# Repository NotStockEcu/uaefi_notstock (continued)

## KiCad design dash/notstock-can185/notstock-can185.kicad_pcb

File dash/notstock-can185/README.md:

# NOT STOCK CAN 1.85

A round board that sits behind the **Waveshare ESP32-S3-Touch-LCD-1.85**
(SKU 28514) on its three M2 holes and turns the car's OBD supply and CAN
into what the round gauge needs. One 4-wire cable from the OBD plug; to
the display the 4-wire cable that comes with it (CAN) and two wires
(power), all soldered to pads on this board.

KiCad 7 project: `notstock-can185.kicad_pro` (schematic, PCB). The KiCad
schematic joins pins by net labels (same name, same net): PDF in
[docs/schematic.pdf](docs/schematic.pdf). The same circuit drawn with wires,
for reading: [docs/readable.png](docs/readable.png). Placement:
[docs/assembly.png](docs/assembly.png).

**State: rev 7, designed, DRC clean (0 errors, 0 unconnected), ready to
order with assembly. Rev 6 built and in the car: the display's touch
needed a hard press there (fine on USB at home), and the PH connector was
hard to crimp. Rev 7: a second LC stage on the display's supply (L2, C9,
C10, C11) and a JST XH 2.5 mm for J1. Rev 4 built (JLCPCB, assembled): the regulator holds
3.8 V on J3 from about 4 V to 14.4 V in (bench, no load); with the display,
the CAN side and in the car not tried yet.** Rev 4 feeds the display through its
battery socket instead of its USB-C (no room for a USB cable). Rev 6
takes its 12 V from OBD pin 1 (terminal 15): on and off with the key.

## How it connects

The display has no plug-on header. What it has, and what this board uses
(Waveshare's schematic and drawing of the board, `ESP32-S3-LCD-1.85`):

| Display | Cable | This board |
| --- | --- | --- |
| battery socket J1, MX1.25 2-pin (1 BAT, 2 GND); seen from the back with the USB-C down, the 2-pin socket on the left | MX1.25 2-pin plug with wires, or two wires soldered to the socket's pins | J3 pads: "+" to BAT, "-" to GND, 3.75 V |
| UART socket, 4-pin 1.0 mm, bottom right (1 RXD/GPIO44, 2 TXD/GPIO43, 3 3V3, 4 GND) | the 4-wire cable that comes with the display, free ends cut to length | J2 pads, marked with the display's names: IO44, IO43, 3V3, GND (CAN, and the display's 3.3 V for the transceiver) |
| three M2 holes (15.73 left, 14.10 up / 14.90 down; 21.27 right) | M2 spacers, 6 to 8 mm | H1..H3 |

The car: J1, JST XH 4-pin, vertical, through hole (12V, GND, CAN-H, CAN-L, marked on the
board).

## On and off with the key: OBD pin 1

OBD pin 16 is permanent +12 V. Pin 1 is free for the maker; VW puts
terminal 15 there (+12 V switched by the key; measured on this T5.1, and
the CANcheck display is powered from it too). The board takes its 12 V
from pin 1, not 16: on with the key, off without it, nothing drawn when
parked. About 0.1 A at 12 V. Terminal 15 stays on while cranking; the
regulator runs down to 4 V input, so the display rides through the dip.

## What is on it

| Block | Parts |
| --- | --- |
| Input | J1 JST XH 4-pin (2.5 mm) through hole, vertical; F1 0.5 A resettable fuse; D1 SS34 against reverse polarity; D2 SMAJ26A against load dump |
| 12 V -> 3.75 V | U1 LMR16006YDDCR (60 V, 0.6 A, 2.1 MHz), L1 22 uH, D3 K16 (60 V 1 A Schottky), 2 x 22 uF out; 39 k / 10 k sets 3.75 V |
| Filter | L2 1 uH, C9 C10 22 uF, C11 100 nF: the regulator's 2.1 MHz some 70 dB down before the display (corner about 30 kHz; the feedback stays before it) |
| 3.75 V out | J3, two solder pads for the wires to the display's battery socket |
| CAN | U2 SN65HVD230 (3.3 V from the display's UART socket, Rs to GND: full speed); D4 NUP2105L ESD; R4/R5/C8 split termination behind JP1, open, not assembled; R6 1 k in RXD |
| Mechanics | Ø 48 mm like the display, the display's three M2 holes |

Termination: JP1 open, R4/R5/C8 not assembled. Measure the resistance
between OBD pins 6 and 14 with the key out: about 60 R, the bus is
terminated at both ends and nothing is needed; about 120 R, only one end
is (on the power box, the T5.1 needed a 120 R at the OBD end to talk):
solder R4 and R5 (any 0805 56..62 R) and bridge JP1, C8 optional.

## Cable to the car

JST XHP-4 housing with SXH-001T-P0.6 crimps on the board side (XH
crimps are bigger than PH and easier by hand; ready-made "XH 2.54 4P"
leads with the crimps on save the crimping); at the OBD
plug: pin 1 +12 V (terminal 15, not pin 16), pin 4 or 5 GND, pin 6
CAN-H, pin 14 CAN-L. CAN-H and
CAN-L twisted.

## Check before ordering

- Which wire is which on the display's cable: the colours mean nothing.
  Plugged into the display, powered from its USB: 3.3 V between the 3V3
  wire and the GND wire. With the display unpowered, the GND wire beeps to
  the USB-C shell. Of the other two, IO44 is on socket pin 1 (next to the
  edge marked 1 or the triangle on the display's silkscreen).
- The battery plug's polarity: ready-made MX1.25 cables come both ways.
  Red is not proof: with the plug in the display, the wire on the
  display's "+" (or BAT) side goes to J3 "+".
- Height: the spacers must clear the display's tallest parts (USB-C, SD
  slot, the 1.0 mm sockets, about 4.5 mm) plus the cables' plugs. The wire
  pads are through holes: solder the wires from the display's side, or
  from the back with the ends trimmed flat.
- Waveshare's drawing was the source of the outline and the holes; hold
  the printed board (1:1 PDF of `docs/top.svg`) against the display first.

## Make it (JLCPCB, with assembly)

Three files in `fab/`:

| File | Where on JLCPCB |
| --- | --- |
| `notstock-can185-gerbers.zip` | "Add gerber file": 2 layers, 1.6 mm, any colour |
| `bom.csv` | PCB Assembly, "Add BOM File" |
| `cpl.csv` | PCB Assembly, "Add CPL File" |

Assembly: top side only, all SMD but J1, a through-hole part: JLCPCB
fits it too (THT assembly, a small extra), or leave it out of the order
and solder its 4 pins by hand. Its pins come out on the display's side:
cut them short (about 1 mm). Every part has its LCSC number in
`bom.csv` (also in the schematic and on the footprints, field "LCSC"):

| Ref | Part | LCSC |
| --- | --- | --- |
| U1 | TI LMR16006YDDCR | C290195 |
| U2 | TI SN65HVD230DR | C12084 |
| D4 | onsemi NUP2105LT1G | C14486 |
| D1 | SS34 (MDD) | C8678 |
| D2 | SMAJ26A | C383018 |
| D3 | GOODWORK K16 (60 V 1 A, SOD-123FL) | C2943756 |
| F1 | SMD1812P050TF/30 (RUILON) | C12559 |
| L1 | Sunlord SWPA4026S220MT | C88254 |
| L2 | Sunlord SWPA4026S1R0NT (1 uH) | C96890 |
| J1 | JST B4B-XH-A(LF)(SN) (vertical, through hole) | C144395 |
| C1 | 4.7 uF 50 V 1206 (Murata) | C77096 |
| C2, C3, C6, C7, C11 | 100 nF 50 V 0603 (YAGEO) | C14663 |
| C4, C5, C9, C10 | 22 uF 16 V 1206 (Samsung) | C90146 |
| R1 | 100 k 0603 | C25803 |
| R2 | 39 k 0603 | C23153 |
| R3 | 10 k 0603 | C25804 |
| R6 | 1 k 0603 | C21190 |

R4, R5 and C8 (the split termination) are not assembled: with JP1 open
they do nothing, and the car's bus is terminated already. For a bench
without a terminator solder them by hand: R4, R5 any 0805 56..62 R 1 %, C8
4.7 nF 0603 (C53987), then bridge JP1.

JP1 is a solder bridge, J2 and J3 pads for wires: not parts. Stock changes: JLCPCB marks a part out
of stock in the BOM step; pick an equivalent there (same value, package,
voltage). The passives and D1 (SS34, C8678) are JLCPCB basic parts, the rest
extended (a small loading fee each). C4, C5, C9, C10 stay 1206 here (the built rev 4
layout); on the 1.32 board they are the basic 0805 C45783.

In the placement preview, check the parts with a direction: U1 (pin 1 dot),
U2 (pin 1 at the notch), D4, J1 (pin 1 square, 12V), D1/D2/D3 (the band towards the "K" side of the
footprint's silkscreen). KiCad and JLCPCB do not always agree on rotations; turn any
that are off in 90° steps there.

## Regenerate

Everything is generated from `tools/design.py` (parts, nets, positions):

```
python3 tools/gen_sch.py                       # the schematic
kicad-cli sch export netlist -o /tmp/n.net notstock-can185.kicad_sch
python3 tools/check_net.py /tmp/n.net          # schematic = design.py
python3 tools/gen_pcb.py --freerouting freerouting-2.0.1.jar
python3 tools/drc_summary.py                   # DRC of the routed board
python3 tools/gen_fab.py                       # fab/ and docs/
python3 tools/gen_readable.py                  # docs/readable.svg
```

Needs KiCad 7 with its python module and libraries, Java 21 and
[Freerouting](https://github.com/freerouting/freerouting) 2.x for the
routing. Freerouting is not deterministic: each run gives a different (and
DRC-checked) routing. Opened in KiCad, the project behaves like any other;
the generators overwrite manual changes, so after editing by hand stop
using them.

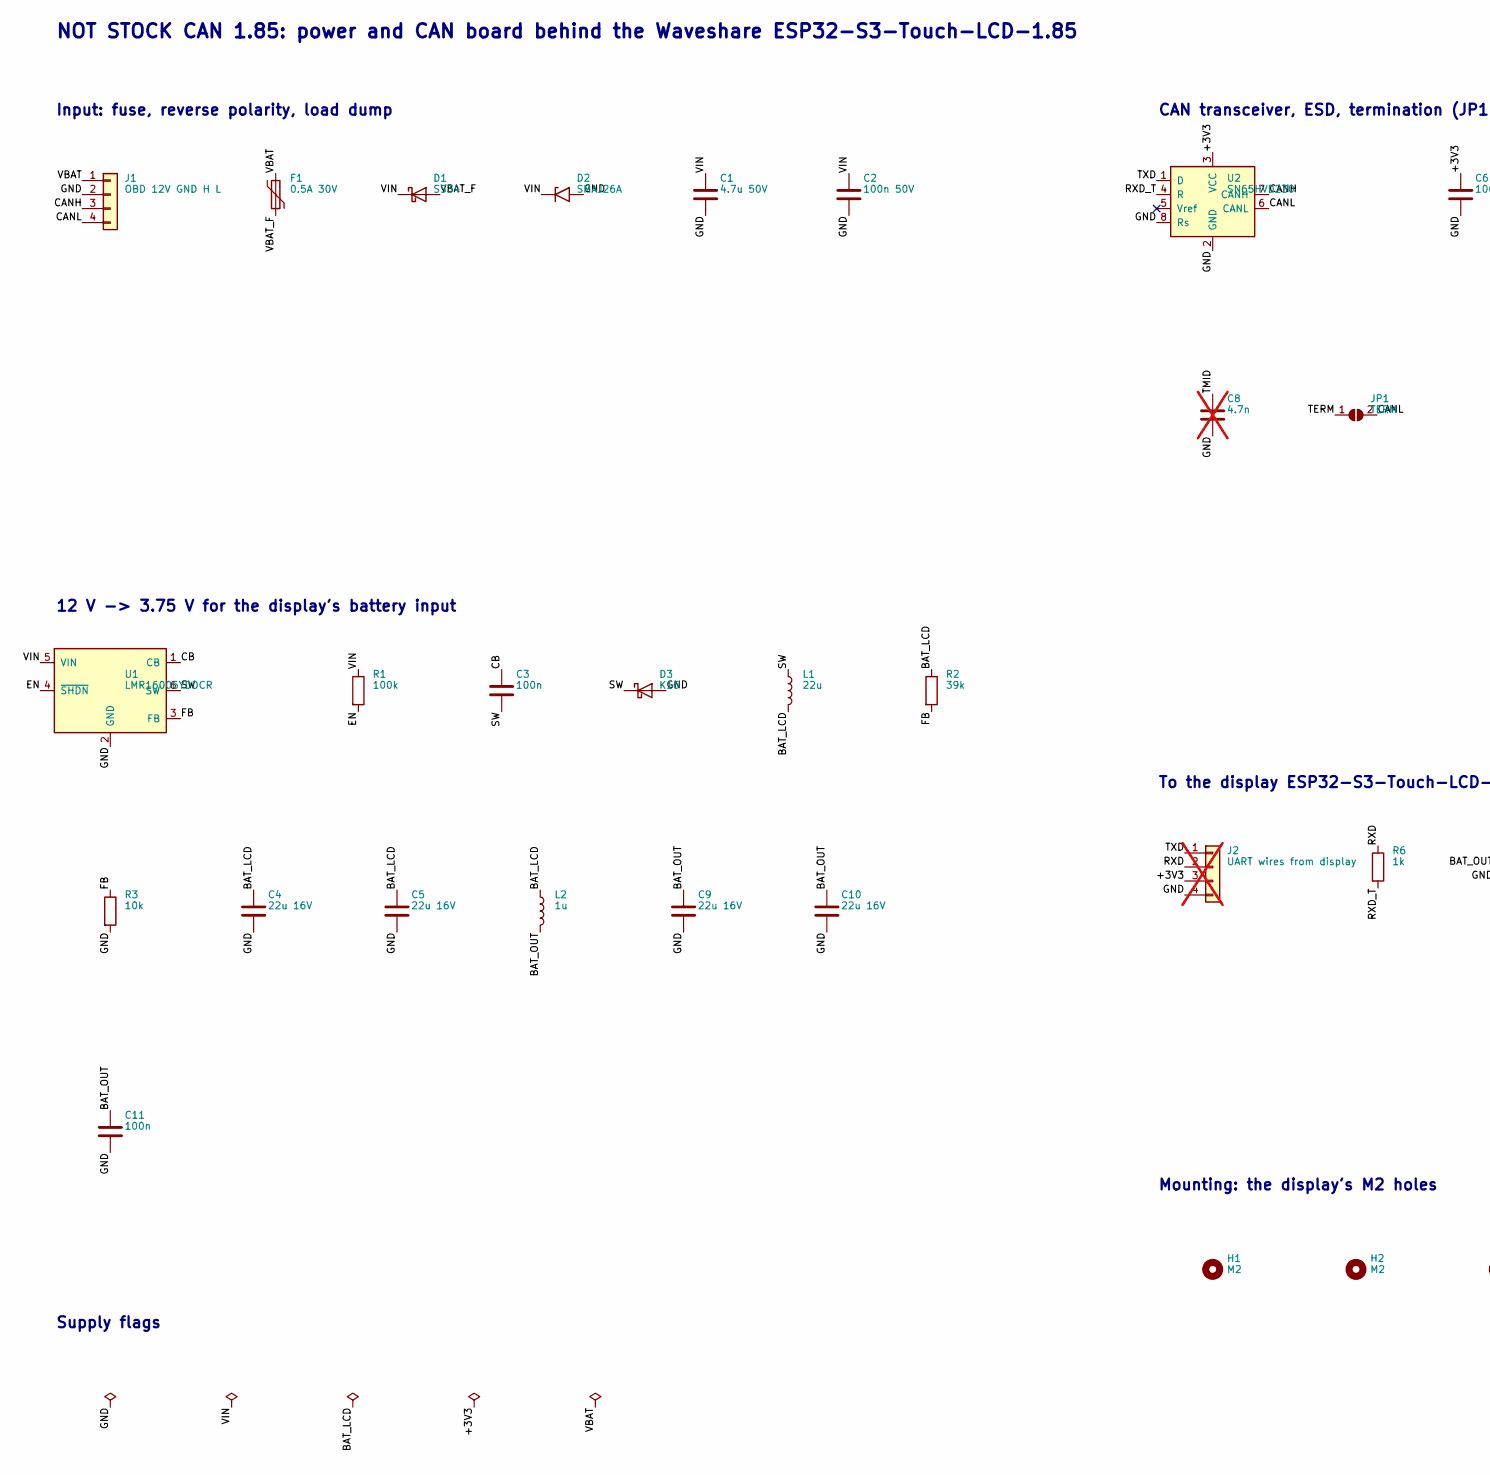
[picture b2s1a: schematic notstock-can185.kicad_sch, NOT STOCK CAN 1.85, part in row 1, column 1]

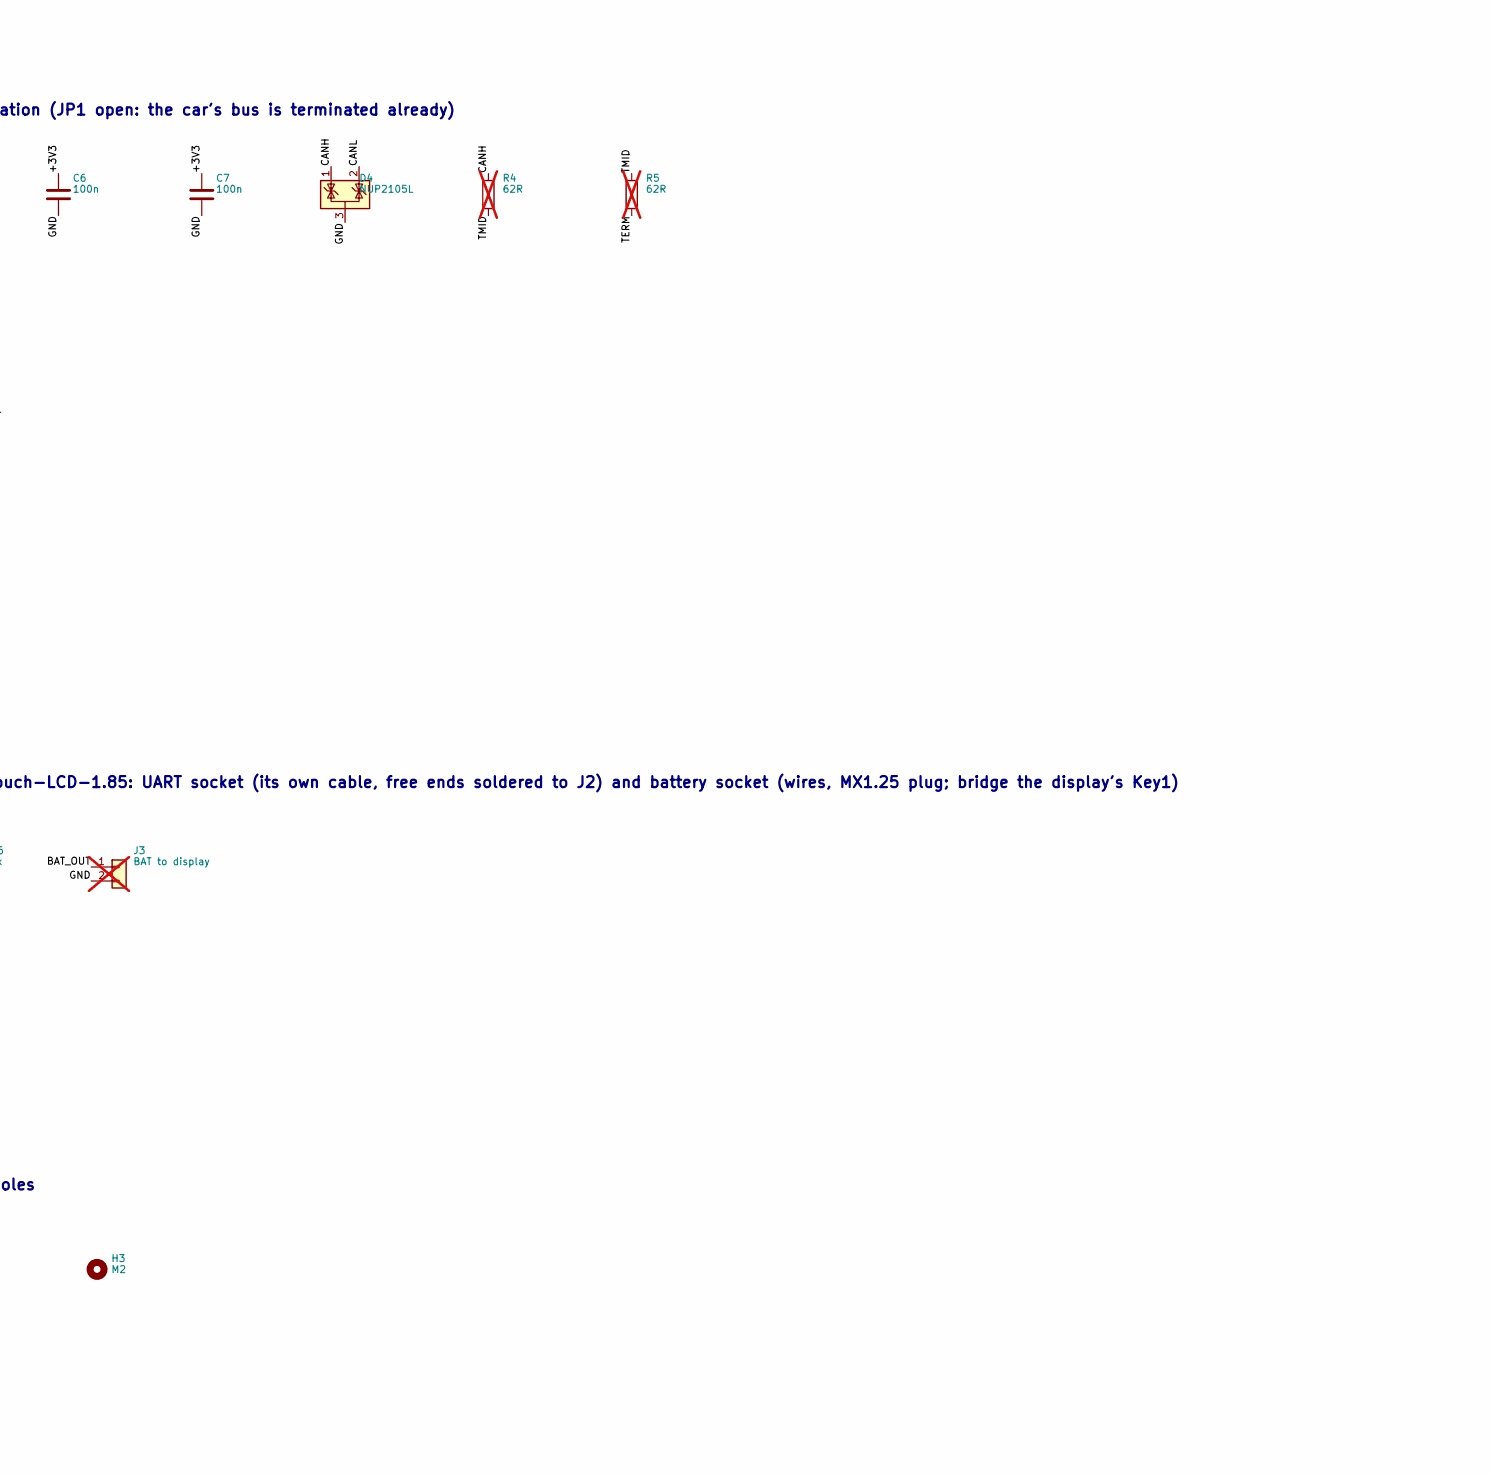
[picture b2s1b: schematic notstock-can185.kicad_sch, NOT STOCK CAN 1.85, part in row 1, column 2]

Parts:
C1: 4.7u 50V; C_1206_3216Metric; MPN Murata GRM31CR71H475KA12L (4.7 uF 50 V 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; LCSC C77096
C2: 100n 50V; C_0603_1608Metric; MPN YAGEO CC0603KRX7R9BB104 (100 nF 50 V); LCSC C14663
C3, C6, C7, C11: 100n; C_0603_1608Metric; MPN YAGEO CC0603KRX7R9BB104 (100 nF 50 V); LCSC C14663
C4, C5, C9, C10: 22u 16V; C_1206_3216Metric; MPN Samsung CL31A226KOHNNNE (22 uF 16 V X5R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; LCSC C90146
C8: 4.7n; C_0603_1608Metric; MPN FH 0603B472K500NT (4.7 nF 50 V X7R); LCSC C53987; not fitted
D1: SS34; D_SMA; MPN MDD SS34 (40 V 3 A); LCSC C8678
D2: SMAJ26A; D_SMA; MPN SMAJ26A; LCSC C383018
D3: K16; D_SOD-123F; MPN GOODWORK K16 (60 V 1 A Schottky, SOD-12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; LCSC C2943756
D4: NUP2105L; SOT-23; MPN onsemi NUP2105LT1G; LCSC C14486
F1: 0.5A 30V; Fuse_1812_4532Metric; MPN RUILON SMD1812P050TF/30 (0.5 A, 30 V); LCSC C12559
H1, H2, H3: M2; MountingHole_2.2mm_M2; MPN M2
J1: OBD 12V GND H L; JST_XH_B4B-XH-A_1x04_P2.50mm_Vertical; MPN JST B4B-XH-A(LF)(SN); LCSC C144395
J2: UART wires from display; SolderWire-0.15sqmm_1x04_P4mm_D0.5mm_OD1.5mm; MPN (wires); not fitted
J3: BAT to display; SolderWire-0.25sqmm_1x02_P4.2mm_D0.65mm_OD1.7mm; MPN (wires); not fitted
JP1: TERM; SolderJumper-2_P1.3mm_Open_Pad1.0x1.5mm; MPN (solder bridge)
L1: 22u; L_Sunlord_SWPA4026S; MPN Sunlord SWPA4026S220MT (22 uH); LCSC C88254
L2: 1u; L_Sunlord_SWPA4026S; MPN Sunlord SWPA4026S1R0NT (1 uH 3 A); LCSC C96890
R1: 100k; R_0603_1608Metric; MPN UNI-ROYAL 0603WAF1003T5E (100 k 1%); LCSC C25803
R2: 39k; R_0603_1608Metric; MPN UNI-ROYAL 0603WAF3902T5E (39 k 1%); LCSC C23153
R3: 10k; R_0603_1608Metric; MPN UNI-ROYAL 0603WAF1002T5E (10 k 1%); LCSC C25804
R4, R5: 62R; R_0805_2012Metric; MPN 62 R 1% 0805; not fitted
R6: 1k; R_0603_1608Metric; MPN UNI-ROYAL 0603WAF1001T5E (1 k 1%); LCSC C21190
U1: LMR16006YDDCR; SOT-23-6; MPN TI LMR16006YDDCR; LCSC C290195
U2: SN65HVD230; SOIC-8_3.9x4.9mm_P1.27mm; MPN TI SN65HVD230DR; LCSC C12084

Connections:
+3V3: C6.1, C7.1, J2.3, U2.3 (VCC)
BAT_LCD: C4.1, C5.1, L1.2, L2.1, R2.1
BAT_OUT: C9.1, C10.1, C11.1, J3.1, L2.2
CANH: D4.1 (K), J1.3, R4.1, U2.7 (CANH)
CANL: D4.2 (K), J1.4, JP1.2 (B), U2.6 (CANL)
CB: C3.1, U1.1 (CB)
EN: R1.2, U1.4 (~SHDN)
FB: R2.2, R3.1, U1.3 (FB)
GND: C1.2, C2.2, C4.2, C5.2, C6.2, C7.2, C8.2, C9.2, C10.2, C11.2, D2.2 (A2), D3.2 (A), D4.3 (A), J1.2, J2.4, J3.2, R3.2, U1.2 (GND), U2.2 (GND), U2.8 (Rs)
RXD: J2.2, R6.1
RXD_T: R6.2, U2.4 (R)
SW: C3.2, D3.1 (K), L1.1, U1.6 (SW)
TERM: JP1.1 (A), R5.2
TMID: C8.1, R4.2, R5.1
TXD: J2.1, U2.1 (D)
VBAT: F1.1, J1.1
VBAT_F: D1.2 (A), F1.2
VIN: C1.1, C2.1, D1.1 (K), D2.1 (A1), R1.1, U1.5 (VIN)

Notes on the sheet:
Input: fuse, reverse polarity, load dump
12 V -> 3.75 V for the display's battery input
CAN transceiver, ESD, termination (JP1 open: the car's bus is terminated already)
To the display ESP32-S3-Touch-LCD-1.85: UART socket (its own cable, free ends soldered to J2) and battery socket (wires, MX1.25 plug; bridge the display's Key1)
Mounting: the display's M2 holes
NOT STOCK CAN 1.85: power and CAN board behind the Waveshare ESP32-S3-Touch-LCD-1.85
Supply flags

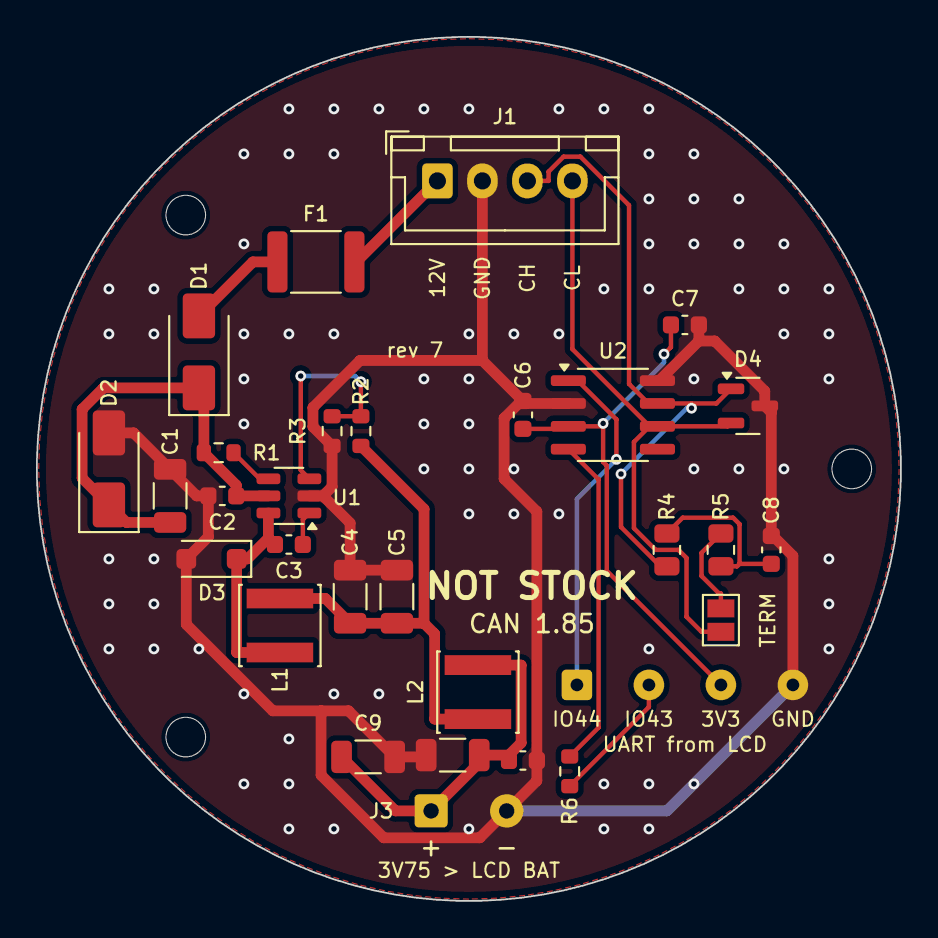
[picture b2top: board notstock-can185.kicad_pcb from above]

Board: 2 copper layers, 48.0 x 48.0 mm, 33 parts (0 on the bottom side), 18 nets.

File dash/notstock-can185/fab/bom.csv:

Comment,Designator,Footprint,LCSC Part #
Murata GRM31CR71H475KA12L (4.7 uF 50 V X7R 1206),C1,C_1206_3216Metric,C77096
YAGEO CC0603KRX7R9BB104 (100 nF 50 V),"C11,C2,C3,C6,C7",C_0603_1608Metric,C14663
Samsung CL31A226KOHNNNE (22 uF 16 V X5R 1206),"C10,C4,C5,C9",C_1206_3216Metric,C90146
MDD SS34 (40 V 3 A),D1,D_SMA,C8678
SMAJ26A,D2,D_SMA,C383018
"GOODWORK K16 (60 V 1 A Schottky, SOD-123FL)",D3,D_SOD-123F,C2943756
onsemi NUP2105LT1G,D4,SOT-23,C14486
"RUILON SMD1812P050TF/30 (0.5 A, 30 V)",F1,Fuse_1812_4532Metric,C12559
JST B4B-XH-A(LF)(SN),J1,JST_XH_B4B-XH-A_1x04_P2.50mm_Vertical,C144395
Sunlord SWPA4026S220MT (22 uH),L1,L_Sunlord_SWPA4026S,C88254
Sunlord SWPA4026S1R0NT (1 uH 3 A),L2,L_Sunlord_SWPA4026S,C96890
UNI-ROYAL 0603WAF1003T5E (100 k 1%),R1,R_0603_1608Metric,C25803
UNI-ROYAL 0603WAF3902T5E (39 k 1%),R2,R_0603_1608Metric,C23153
UNI-ROYAL 0603WAF1002T5E (10 k 1%),R3,R_0603_1608Metric,C25804
UNI-ROYAL 0603WAF1001T5E (1 k 1%),R6,R_0603_1608Metric,C21190
TI LMR16006YDDCR,U1,SOT-23-6,C290195
TI SN65HVD230DR,U2,SOIC-8_3.9x4.9mm_P1.27mm,C12084

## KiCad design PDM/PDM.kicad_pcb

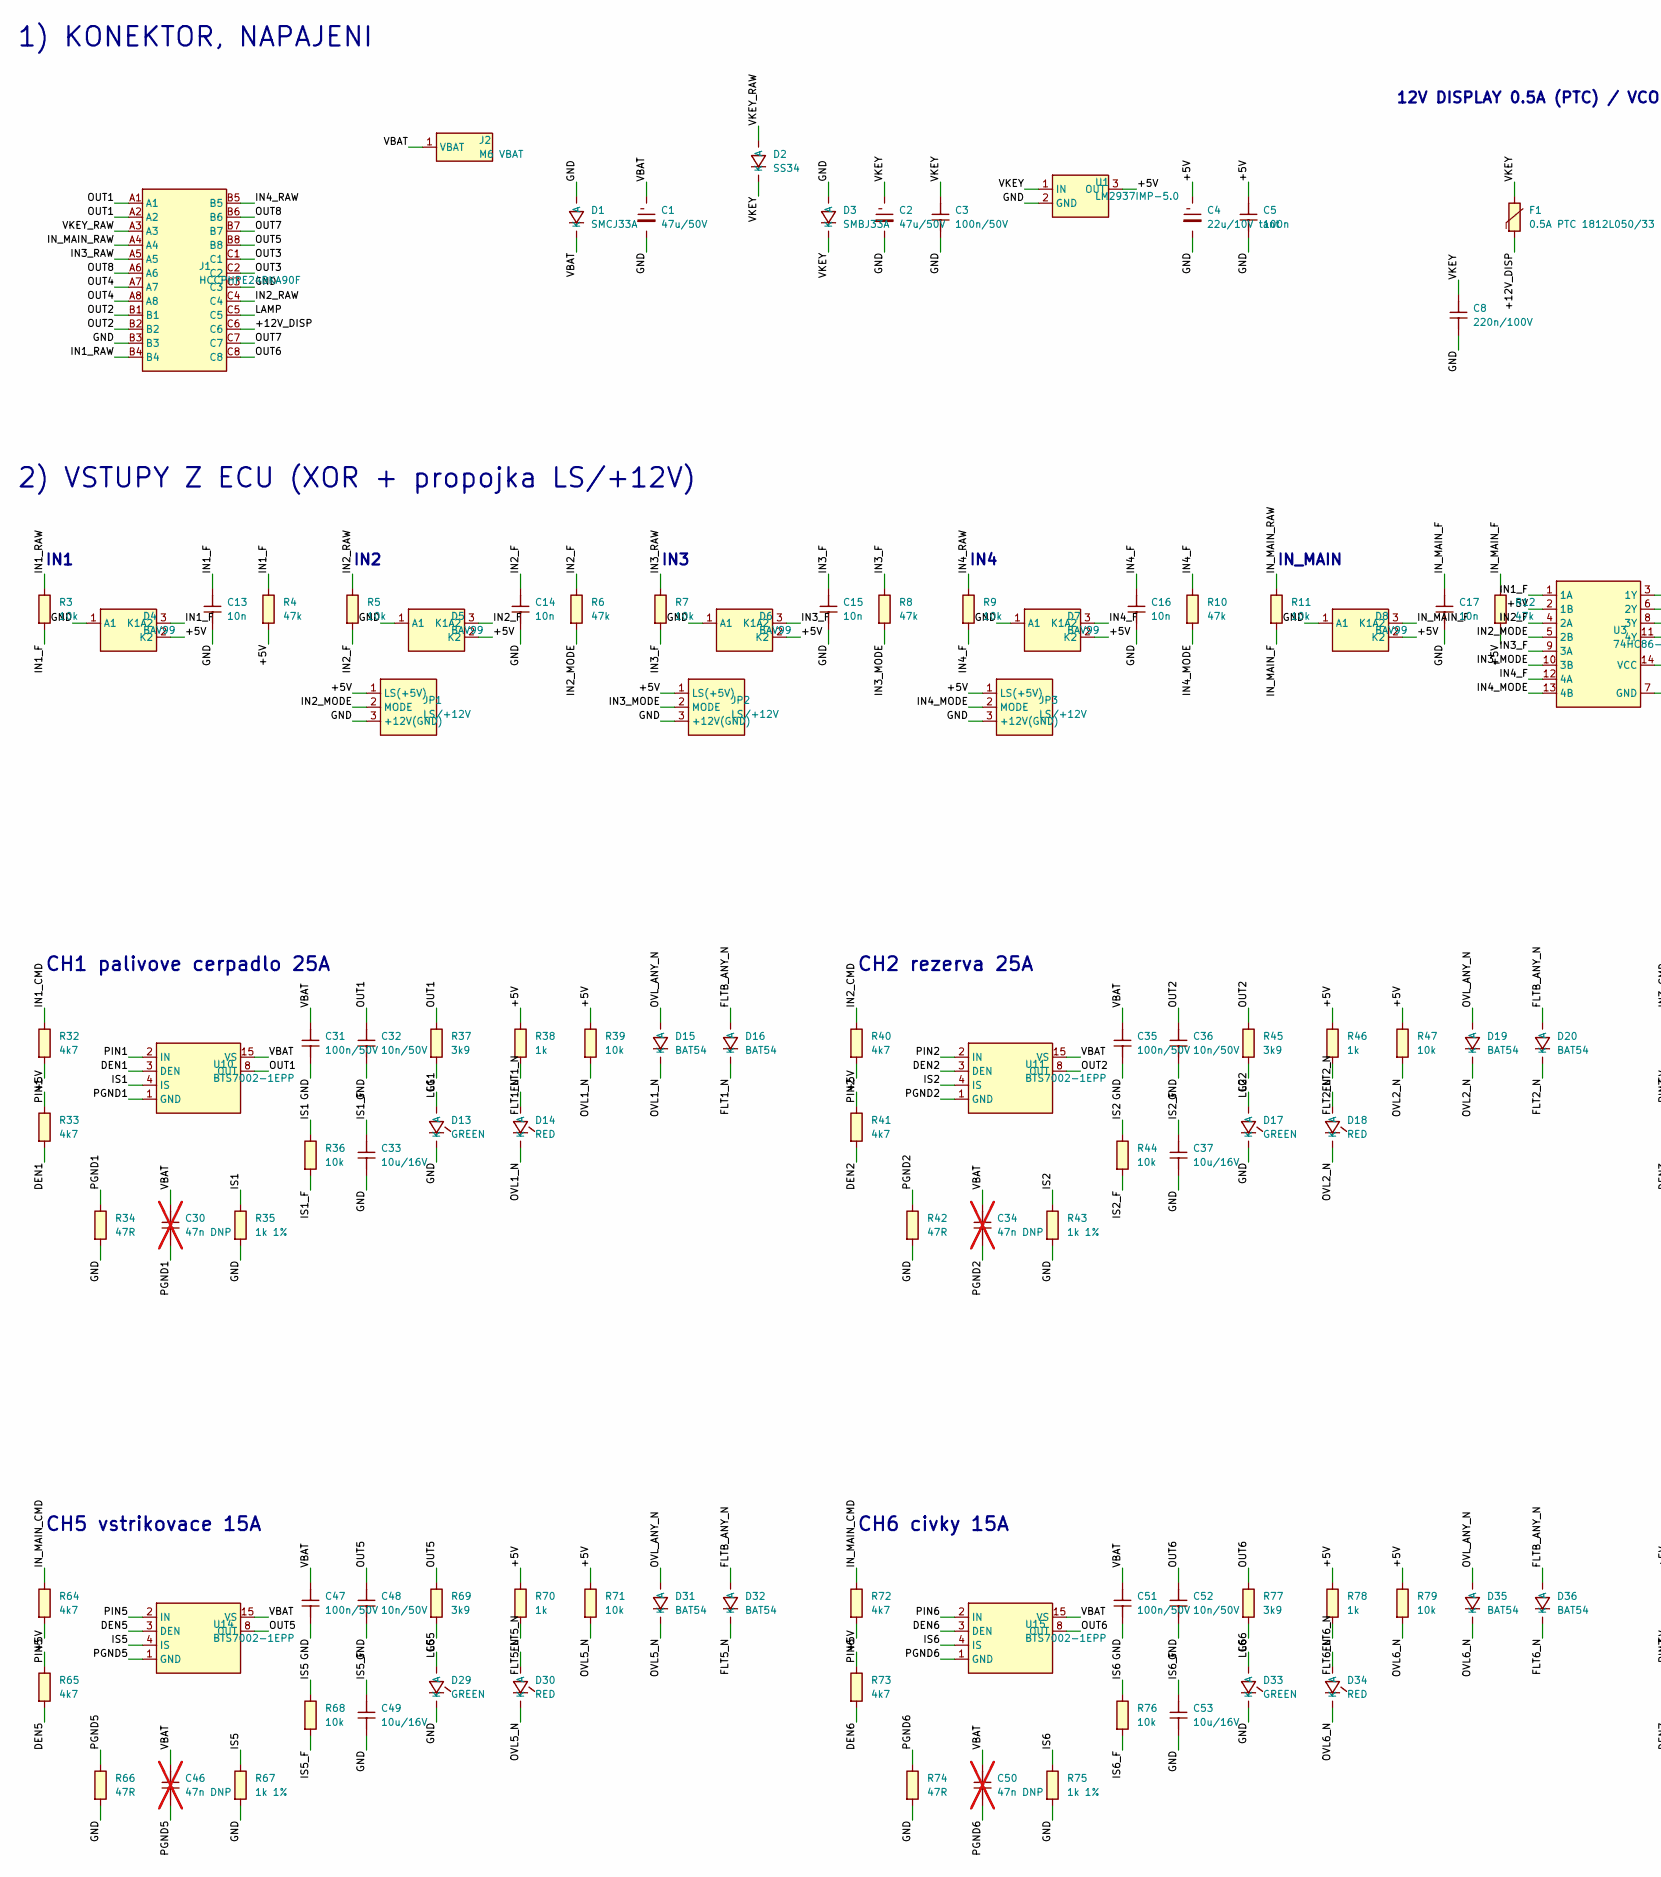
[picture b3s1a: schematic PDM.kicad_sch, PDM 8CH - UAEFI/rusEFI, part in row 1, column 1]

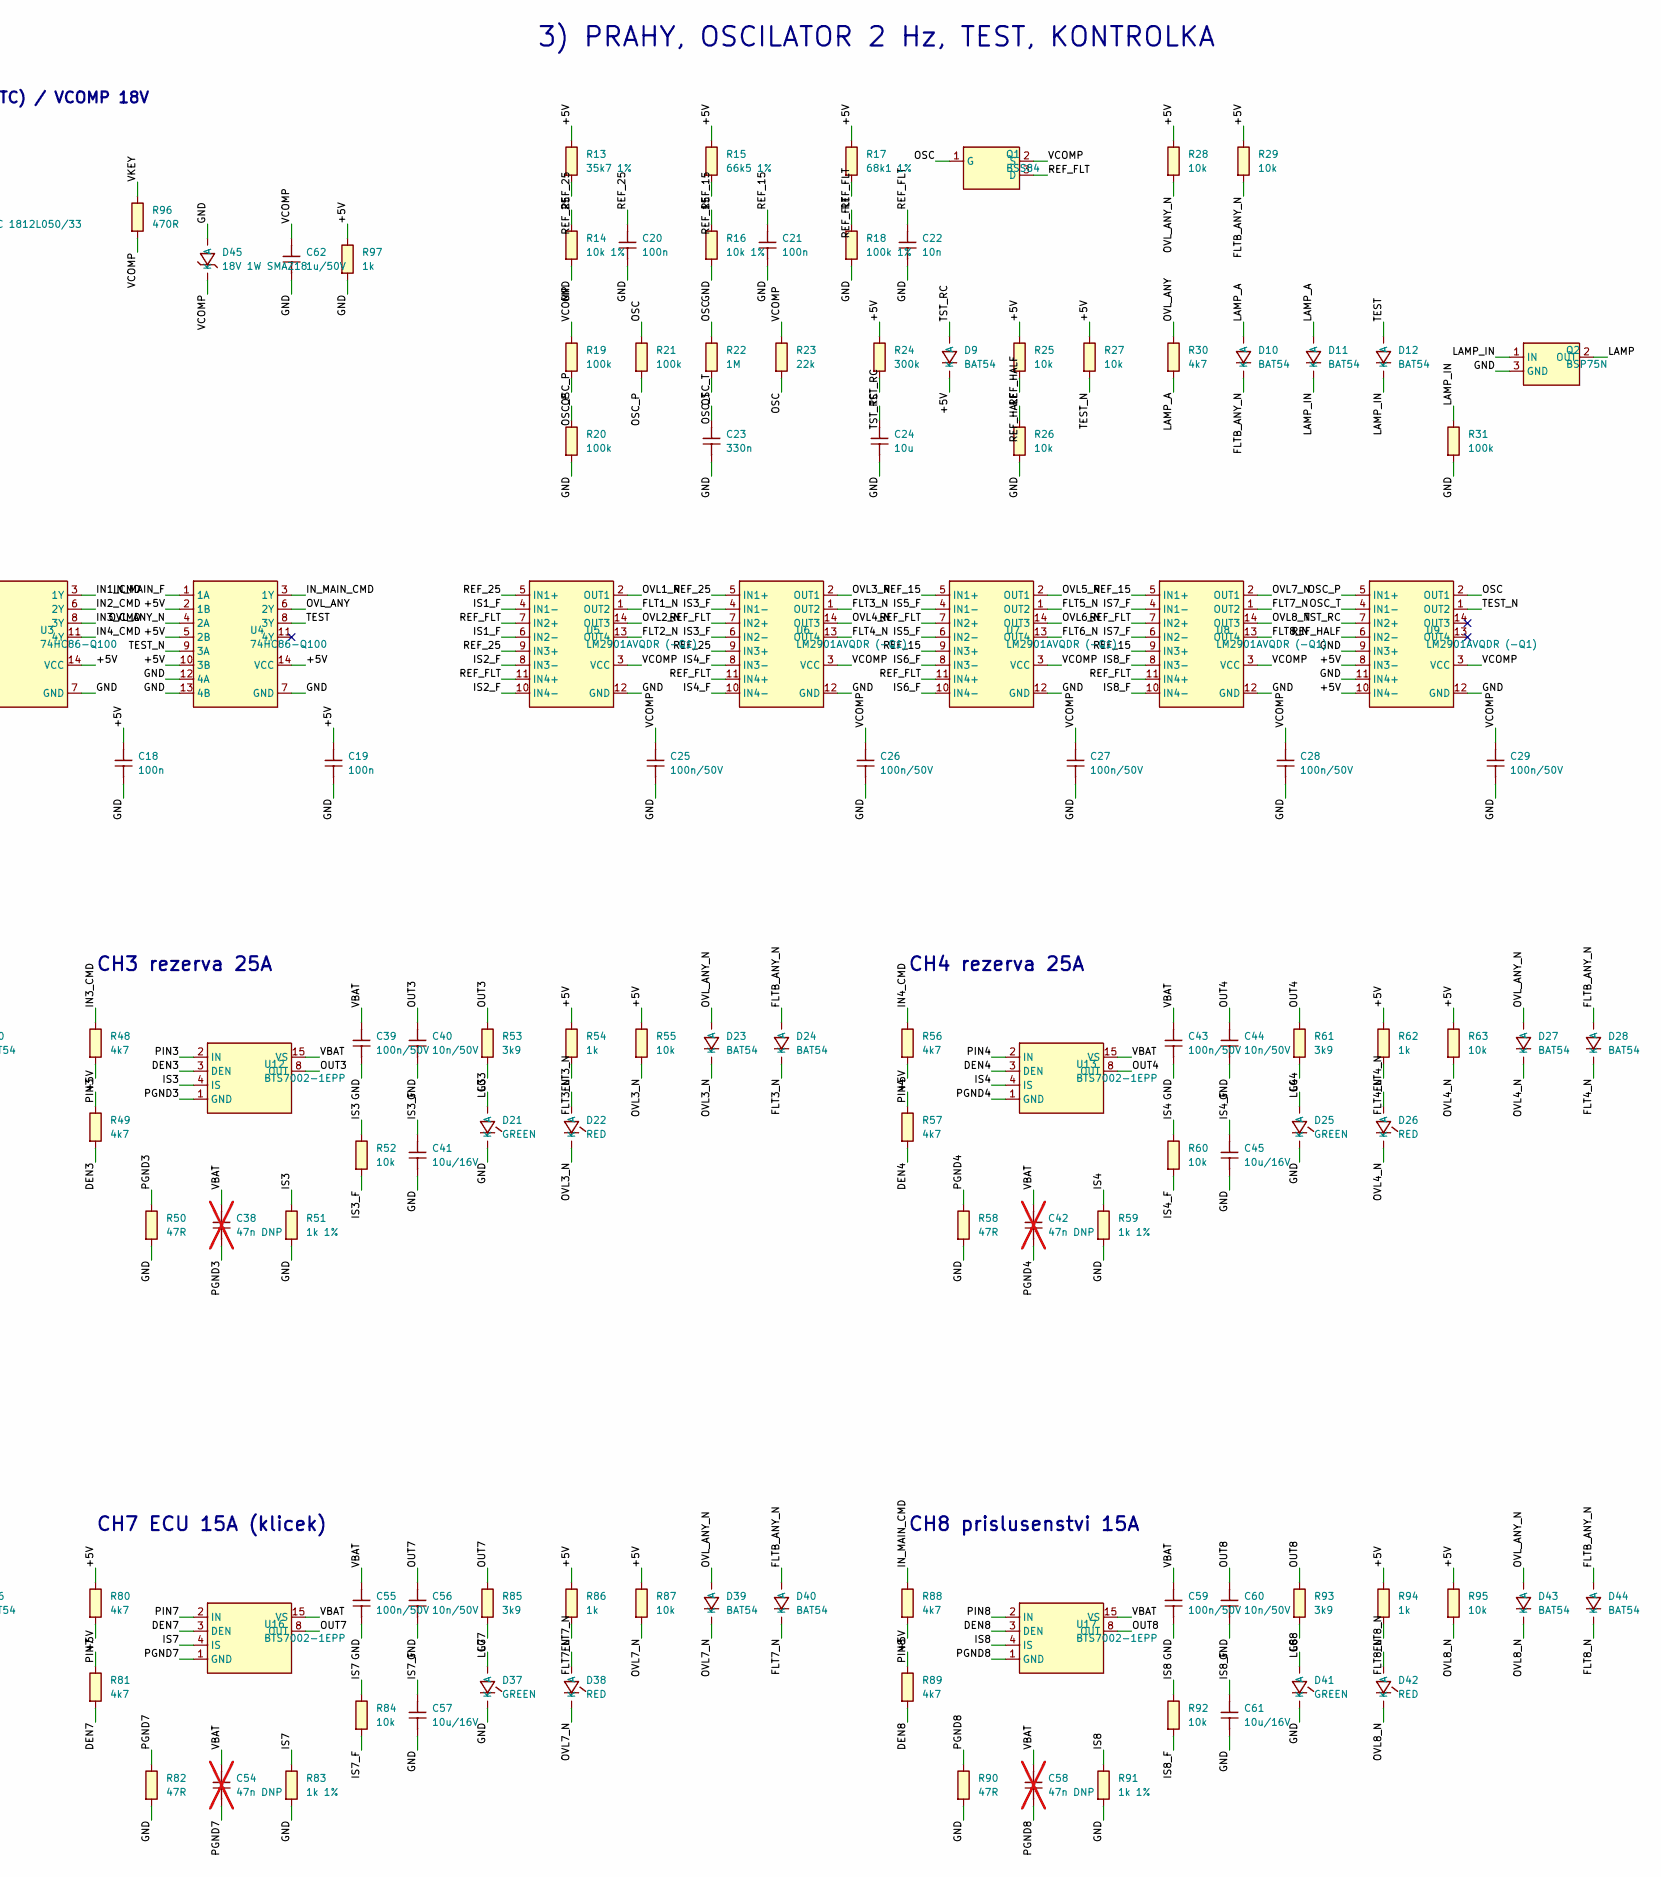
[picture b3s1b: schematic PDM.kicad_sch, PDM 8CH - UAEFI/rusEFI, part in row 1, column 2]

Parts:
C1, C2: 47u/50V; CP_Elec_8x10; MPN EEE-FK1H470P
C3, C25, C26, C27, C28, C29, C31, C35, C39, C43, C47, C51, C55, C59: 100n/50V; C_0805_2012Metric; MPN CL21B104KBCNNNC
C4: 22u/10V tant; CP_EIA-3528-21_Kemet-B; MPN T491B226K010AT
C5, C18, C19, C20, C21: 100n; C_0805_2012Metric; MPN CL21B104KBCNNNC
C8: 220n/100V; C_0805_2012Metric; MPN GCM21BR72A224KA37L
C13, C14, C15, C16, C17, C22: 10n; C_0805_2012Metric; MPN CL21B103KBANNNC
C23: 330n; C_0805_2012Metric; MPN CL21B334KBFNNNE
C24: 10u; C_0805_2012Metric; MPN CL21A106KOQNNNE
C30, C34, C38, C42, C46, C50, C54, C58: 47n DNP; C_0805_2012Metric; MPN CL21B473KBANNNC; not fitted
C32, C36, C40, C44, C48, C52, C56, C60: 10n/50V; C_0805_2012Metric; MPN CL21B103KBANNNC
C33, C37, C41, C45, C49, C53, C57, C61: 10u/16V; C_0805_2012Metric; MPN CL21A106KOQNNNE
C62: 1u/50V; C_0805_2012Metric; MPN CL21B105KBFNNNE
D1: SMCJ33A; D_SMC; MPN SMCJ33A
D2: SS34; D_SMA; MPN SS34-E3/61T
D3: SMBJ33A; D_SMB; MPN SMBJ33A
D4, D5, D6, D7, D8: BAV99; SOT-23; MPN BAV99,215
D9, D10, D11, D12, D15, D16, D19, D20, D23, D24, D27, D28, D31, D32, D35, D36, D39, D40, D43, D44: BAT54; SOT-23; MPN BAT54,215
D13, D17, D21, D25, D29, D33, D37, D41: GREEN; LED_0805_2012Metric; MPN 150080GS75000
D14, D18, D22, D26, D30, D34, D38, D42: RED; LED_0805_2012Metric; MPN 150080RS75000
D45: 18V 1W SMAZ18; D_SMA; MPN SMAZ18-13-F
F1: 0.5A PTC 1812L050/33; Fuse_1812_4532Metric; MPN 1812L050/33MR
J1: HCCPHPE24BKA90F; Aptiv_SICMA_HCCPHPE24BKA90F_24P_RA; MPN HCCPHPE24BKA90F
J2: M6 VBAT; MountingHole_6.4mm_M6_Pad_Via
JP1, JP2, JP3: LS/+12V; PinHeader_1x03_P2.54mm_Vertical; MPN 61300311121
Q1: BSS84; SOT-23; MPN BSS84,215
Q2: BSP75N; SOT-223-3_TabPin2; MPN BSP75NH6327XTSA1
R3, R5, R7, R9, R11, R25, R26, R27, R28, R29, R36, R39, R44, R47, R52, R55, R60, R63, R68, R71, R76, R79, R84, R87, R92, R95: 10k; R_0805_2012Metric; MPN RC0805FR-0710KL
R4, R6, R8, R10, R12: 47k; R_0805_2012Metric; MPN RC0805FR-0747KL
R13: 35k7 1%; R_0805_2012Metric; MPN RC0805FR-0735K7L
R14, R16: 10k 1%; R_0805_2012Metric; MPN RC0805FR-0710KL
R15: 66k5 1%; R_0805_2012Metric; MPN RC0805FR-0766K5L
R17: 68k1 1%; R_0805_2012Metric; MPN RC0805FR-0768K1L
R18: 100k 1%; R_0805_2012Metric; MPN RC0805FR-07100KL
R19, R20, R21, R31: 100k; R_0805_2012Metric; MPN RC0805FR-07100KL
R22: 1M; R_0805_2012Metric; MPN RC0805FR-071ML
R23: 22k; R_0805_2012Metric; MPN RC0805FR-0722KL
R24: 300k; R_0805_2012Metric; MPN RC0805FR-07300KL
R30, R32, R33, R40, R41, R48, R49, R56, R57, R64, R65, R72, R73, R80, R81, R88, R89: 4k7; R_0805_2012Metric; MPN RC0805FR-074K7L
R34, R42, R50, R58, R66, R74, R82, R90: 47R; R_0805_2012Metric; MPN RC0805FR-0747RL
R35, R43, R51, R59, R67, R75, R83, R91: 1k 1%; R_0805_2012Metric; MPN RC0805FR-071KL
R37, R45, R53, R61, R69, R77, R85, R93: 3k9; R_0805_2012Metric; MPN RC0805FR-073K9L
R38, R46, R54, R62, R70, R78, R86, R94, R97: 1k; R_0805_2012Metric; MPN RC0805FR-071KL
R96: 470R; R_1206_3216Metric; MPN RC1206FR-07470RL
U1: LM2937IMP-5.0; SOT-223-3_TabPin2; MPN LM2937IMP-5.0/NOPB
U3, U4: 74HC86-Q100; SOIC-14_3.9x8.7mm_P1.27mm; MPN 74HC86D-Q100J
U5, U6, U7, U8, U9: LM2901AVQDR (-Q1); SOIC-14_3.9x8.7mm_P1.27mm; MPN LM2901AVQDRQ1
U10, U11, U12, U13, U14, U15, U16, U17: BTS7002-1EPP; Infineon_PG-TSDSO-14-22; MPN BTS70021EPPXUMA1

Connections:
/+5V: C4.1, C5.1, C18.1, C19.1, D4.2 (K2), D5.2 (K2), D6.2 (K2), D7.2 (K2), D8.2 (K2), D9.3 (K), JP1.1 (LS(+5V)), JP2.1 (LS(+5V)), JP3.1 (LS(+5V)), R4.2, R12.2, R13.1, R15.1, R17.1, R24.1, R25.1, R27.1, R28.1, R29.1, R33.1, R38.1, R39.1, R41.1, R46.1, R47.1, R49.1, R54.1, R55.1, R57.1, R62.1, R63.1, R65.1, R70.1, R71.1, R73.1, R78.1, R79.1, R80.1, R81.1, R86.1, R87.1, R89.1, R94.1, R95.1, R97.1, U1.3 (OUT), U3.2 (1B), U3.14 (VCC), U4.2 (1B), U4.5 (2B), U4.10 (3B), U4.14 (VCC), U9.8 (IN3-), U9.10 (IN4-)
/+12V_DISP: F1.2, J1.C6
/DEN1: R33.2, U10.3 (DEN)
/DEN2: R41.2, U11.3 (DEN)
/DEN3: R49.2, U12.3 (DEN)
/DEN4: R57.2, U13.3 (DEN)
/DEN5: R65.2, U14.3 (DEN)
/DEN6: R73.2, U15.3 (DEN)
/DEN7: R81.2, U16.3 (DEN)
/DEN8: R89.2, U17.3 (DEN)
/FLT1_N: D14.2 (A), D16.3 (K), R38.2, U5.1 (OUT2)
/FLT2_N: D18.2 (A), D20.3 (K), R46.2, U5.13 (OUT4)
/FLT3_N: D22.2 (A), D24.3 (K), R54.2, U6.1 (OUT2)
/FLT4_N: D26.2 (A), D28.3 (K), R62.2, U6.13 (OUT4)
/FLT5_N: D30.2 (A), D32.3 (K), R70.2, U7.1 (OUT2)
/FLT6_N: D34.2 (A), D36.3 (K), R78.2, U7.13 (OUT4)
/FLT7_N: D38.2 (A), D40.3 (K), R86.2, U8.1 (OUT2)
/FLT8_N: D42.2 (A), D44.3 (K), R94.2, U8.13 (OUT4)
/FLTB_ANY_N: D10.3 (K), D16.1 (A), D20.1 (A), D24.1 (A), D28.1 (A), D32.1 (A), D36.1 (A), D40.1 (A), D44.1 (A), R29.2
/GND: C1.2, C2.2, C3.2, C4.2, C5.2, C8.2, C13.2, C14.2, C15.2, C16.2, C17.2, C18.2, C19.2, C20.2, C21.2, C22.2, C23.2, C24.2, C25.2, C26.2, C27.2, C28.2, C29.2, C31.2, C32.2, C33.2, C35.2, C36.2, C37.2, C39.2, C40.2, C41.2, C43.2, C44.2, C45.2, C47.2, C48.2, C49.2, C51.2, C52.2, C53.2, C55.2, C56.2, C57.2, C59.2, C60.2, C61.2, C62.2, D1.2 (A), D3.2 (A), D4.1 (A1), D5.1 (A1), D6.1 (A1), D7.1 (A1), D8.1 (A1), D13.1 (K), D17.1 (K), D21.1 (K), D25.1 (K), D29.1 (K), D33.1 (K), D37.1 (K), D41.1 (K), D45.2 (A), J1.B3, J1.C3, JP1.3 (+12V(GND)), JP2.3 (+12V(GND)), JP3.3 (+12V(GND)), Q2.3 (GND), R14.2, R16.2, R18.2, R20.2, R26.2, R31.2, R34.2, R35.2, R42.2, R43.2, R50.2, R51.2, R58.2, R59.2, R66.2, R67.2, R74.2, R75.2, R82.2, R83.2, R90.2, R91.2, R97.2, U1.2 (GND), U3.7 (GND), U4.7 (GND), U4.12 (4A), U4.13 (4B), U5.12 (GND), U6.12 (GND), U7.12 (GND), U8.12 (GND), U9.9 (IN3+), U9.11 (IN4+), U9.12 (GND)
/IN1_CMD: R32.1, U3.3 (1Y)
/IN1_F: C13.1, D4.3 (K1A2), R3.2, R4.1, U3.1 (1A)
/IN1_RAW: J1.B4, R3.1
/IN2_CMD: R40.1, U3.6 (2Y)
/IN2_F: C14.1, D5.3 (K1A2), R5.2, R6.1, U3.4 (2A)
/IN2_MODE: JP1.2 (MODE), R6.2, U3.5 (2B)
/IN2_RAW: J1.C4, R5.1
/IN3_CMD: R48.1, U3.8 (3Y)
/IN3_F: C15.1, D6.3 (K1A2), R7.2, R8.1, U3.9 (3A)
/IN3_MODE: JP2.2 (MODE), R8.2, U3.10 (3B)
/IN3_RAW: J1.A5, R7.1
/IN4_CMD: R56.1, U3.11 (4Y)
/IN4_F: C16.1, D7.3 (K1A2), R9.2, R10.1, U3.12 (4A)
/IN4_MODE: JP3.2 (MODE), R10.2, U3.13 (4B)
/IN4_RAW: J1.B5, R9.1
/IN_MAIN_CMD: R64.1, R72.1, R88.1, U4.3 (1Y)
/IN_MAIN_F: C17.1, D8.3 (K1A2), R11.2, R12.1, U4.1 (1A)
/IN_MAIN_RAW: J1.A4, R11.1
/IS1: R35.1, R36.1, U10.4 (IS)
/IS1_F: C33.1, R36.2, U5.4 (IN1-), U5.6 (IN2-)
/IS2: R43.1, R44.1, U11.4 (IS)
/IS2_F: C37.1, R44.2, U5.8 (IN3-), U5.10 (IN4-)
/IS3: R51.1, R52.1, U12.4 (IS)
/IS3_F: C41.1, R52.2, U6.4 (IN1-), U6.6 (IN2-)
/IS4: R59.1, R60.1, U13.4 (IS)
/IS4_F: C45.1, R60.2, U6.8 (IN3-), U6.10 (IN4-)
/IS5: R67.1, R68.1, U14.4 (IS)
/IS5_F: C49.1, R68.2, U7.4 (IN1-), U7.6 (IN2-)
/IS6: R75.1, R76.1, U15.4 (IS)
/IS6_F: C53.1, R76.2, U7.8 (IN3-), U7.10 (IN4-)
/IS7: R83.1, R84.1, U16.4 (IS)
/IS7_F: C57.1, R84.2, U8.4 (IN1-), U8.6 (IN2-)
/IS8: R91.1, R92.1, U17.4 (IS)
/IS8_F: C61.1, R92.2, U8.8 (IN3-), U8.10 (IN4-)
/LAMP: J1.C5, Q2.2 (OUT)
/LAMP_A: D10.1 (A), D11.1 (A), R30.2
/LAMP_IN: D11.3 (K), D12.3 (K), Q2.1 (IN), R31.1
/LG1: D13.2 (A), R37.2
/LG2: D17.2 (A), R45.2
/LG3: D21.2 (A), R53.2
/LG4: D25.2 (A), R61.2
/LG5: D29.2 (A), R69.2
/LG6: D33.2 (A), R77.2
/LG7: D37.2 (A), R85.2
/LG8: D41.2 (A), R93.2
/OSC: Q1.1 (G), R21.1, R22.1, R23.2, U9.2 (OUT1)
/OSC_P: R19.2, R20.1, R21.2, U9.5 (IN1+)
/OSC_T: C23.1, R22.2, U9.4 (IN1-)
/OUT1: C32.1, J1.A1, J1.A2, R37.1, U10.8 (OUT), U10.9 (OUT), U10.10 (OUT), U10.12 (OUT), U10.13 (OUT), U10.14 (OUT)
/OUT2: C36.1, J1.B1, J1.B2, R45.1, U11.8 (OUT), U11.9 (OUT), U11.10 (OUT), U11.12 (OUT), U11.13 (OUT), U11.14 (OUT)
/OUT3: C40.1, J1.C1, J1.C2, R53.1, U12.8 (OUT), U12.9 (OUT), U12.10 (OUT), U12.12 (OUT), U12.13 (OUT), U12.14 (OUT)
/OUT4: C44.1, J1.A7, J1.A8, R61.1, U13.8 (OUT), U13.9 (OUT), U13.10 (OUT), U13.12 (OUT), U13.13 (OUT), U13.14 (OUT)
/OUT5: C48.1, J1.B8, R69.1, U14.8 (OUT), U14.9 (OUT), U14.10 (OUT), U14.12 (OUT), U14.13 (OUT), U14.14 (OUT)
/OUT6: C52.1, J1.C8, R77.1, U15.8 (OUT), U15.9 (OUT), U15.10 (OUT), U15.12 (OUT), U15.13 (OUT), U15.14 (OUT)
/OUT7: C56.1, J1.B7, J1.C7, R85.1, U16.8 (OUT), U16.9 (OUT), U16.10 (OUT), U16.12 (OUT), U16.13 (OUT), U16.14 (OUT)
/OUT8: C60.1, J1.A6, J1.B6, R93.1, U17.8 (OUT), U17.9 (OUT), U17.10 (OUT), U17.12 (OUT), U17.13 (OUT), U17.14 (OUT)
/OVL1_N: D14.1 (K), D15.3 (K), R39.2, U5.2 (OUT1)
/OVL2_N: D18.1 (K), D19.3 (K), R47.2, U5.14 (OUT3)
/OVL3_N: D22.1 (K), D23.3 (K), R55.2, U6.2 (OUT1)
/OVL4_N: D26.1 (K), D27.3 (K), R63.2, U6.14 (OUT3)
/OVL5_N: D30.1 (K), D31.3 (K), R71.2, U7.2 (OUT1)
/OVL6_N: D34.1 (K), D35.3 (K), R79.2, U7.14 (OUT3)
/OVL7_N: D38.1 (K), D39.3 (K), R87.2, U8.2 (OUT1)
/OVL8_N: D42.1 (K), D43.3 (K), R95.2, U8.14 (OUT3)
/OVL_ANY: R30.1, U4.6 (2Y)
/OVL_ANY_N: D15.1 (A), D19.1 (A), D23.1 (A), D27.1 (A), D31.1 (A), D35.1 (A), D39.1 (A), D43.1 (A), R28.2, U4.4 (2A)
/PGND1: C30.2, R34.1, U10.1 (GND)
/PGND2: C34.2, R42.1, U11.1 (GND)
/PGND3: C38.2, R50.1, U12.1 (GND)
/PGND4: C42.2, R58.1, U13.1 (GND)
/PGND5: C46.2, R66.1, U14.1 (GND)
/PGND6: C50.2, R74.1, U15.1 (GND)
/PGND7: C54.2, R82.1, U16.1 (GND)
/PGND8: C58.2, R90.1, U17.1 (GND)
/PIN1: R32.2, U10.2 (IN)
/PIN2: R40.2, U11.2 (IN)
/PIN3: R48.2, U12.2 (IN)
/PIN4: R56.2, U13.2 (IN)
/PIN5: R64.2, U14.2 (IN)
/PIN6: R72.2, U15.2 (IN)
/PIN7: R80.2, U16.2 (IN)
/PIN8: R88.2, U17.2 (IN)
/REF_15: C21.1, R15.2, R16.1, U7.5 (IN1+), U7.9 (IN3+), U8.5 (IN1+), U8.9 (IN3+)
/REF_25: C20.1, R13.2, R14.1, U5.5 (IN1+), U5.9 (IN3+), U6.5 (IN1+), U6.9 (IN3+)
/REF_FLT: C22.1, Q1.3 (D), R17.2, R18.1, U5.7 (IN2+), U5.11 (IN4+), U6.7 (IN2+), U6.11 (IN4+), U7.7 (IN2+), U7.11 (IN4+), U8.7 (IN2+), U8.11 (IN4+)
/REF_HALF: R25.2, R26.1, U9.6 (IN2-)
/TEST: D12.1 (A), U4.8 (3Y)
/TEST_N: R27.2, U4.9 (3A), U9.1 (OUT2)
/TST_RC: C24.1, D9.1 (A), R24.2, U9.7 (IN2+)
/VBAT: C1.1, C30.1, C31.1, C34.1, C35.1, C38.1, C39.1, C42.1, C43.1, C46.1, C47.1, C50.1, C51.1, C54.1, C55.1, C58.1, C59.1, D1.1 (K), J2.1, U10.15 (VS), U11.15 (VS), U12.15 (VS), U13.15 (VS), U14.15 (VS), U15.15 (VS), U16.15 (VS), U17.15 (VS)
/VCOMP: C25.1, C26.1, C27.1, C28.1, C29.1, C62.1, D45.1 (K), Q1.2 (S), R19.1, R23.1, R96.2, U5.3 (VCC), U6.3 (VCC), U7.3 (VCC), U8.3 (VCC), U9.3 (VCC)
/VKEY: C2.1, C3.1, C8.1, D2.1 (K), D3.1 (K), F1.1, R96.1, U1.1 (IN)
/VKEY_RAW: D2.2 (A), J1.A3

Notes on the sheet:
1) KONEKTOR, NAPAJENI
12V DISPLAY 0.5A (PTC) / VCOMP 18V
2) VSTUPY Z ECU (XOR + propojka LS/+12V)
IN1
IN2
IN3
IN4
IN_MAIN
3) PRAHY, OSCILATOR 2 Hz, TEST, KONTROLKA
CH1 palivove cerpadlo 25A
CH2 rezerva 25A
CH3 rezerva 25A
CH4 rezerva 25A
CH5 vstrikovace 15A
CH6 civky 15A
CH7 ECU 15A (klicek)
CH8 prislusenstvi 15A
